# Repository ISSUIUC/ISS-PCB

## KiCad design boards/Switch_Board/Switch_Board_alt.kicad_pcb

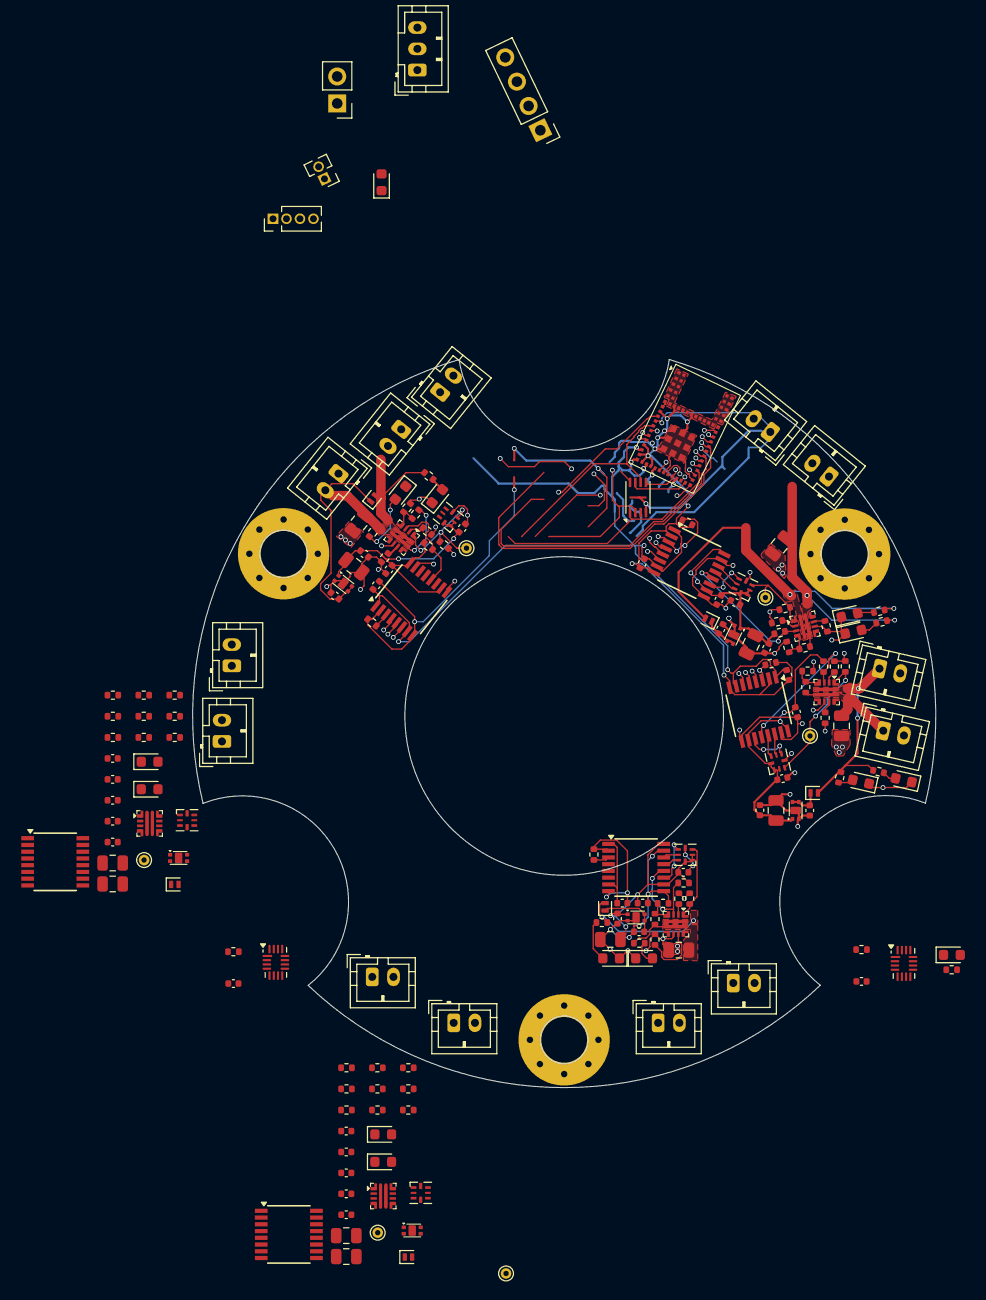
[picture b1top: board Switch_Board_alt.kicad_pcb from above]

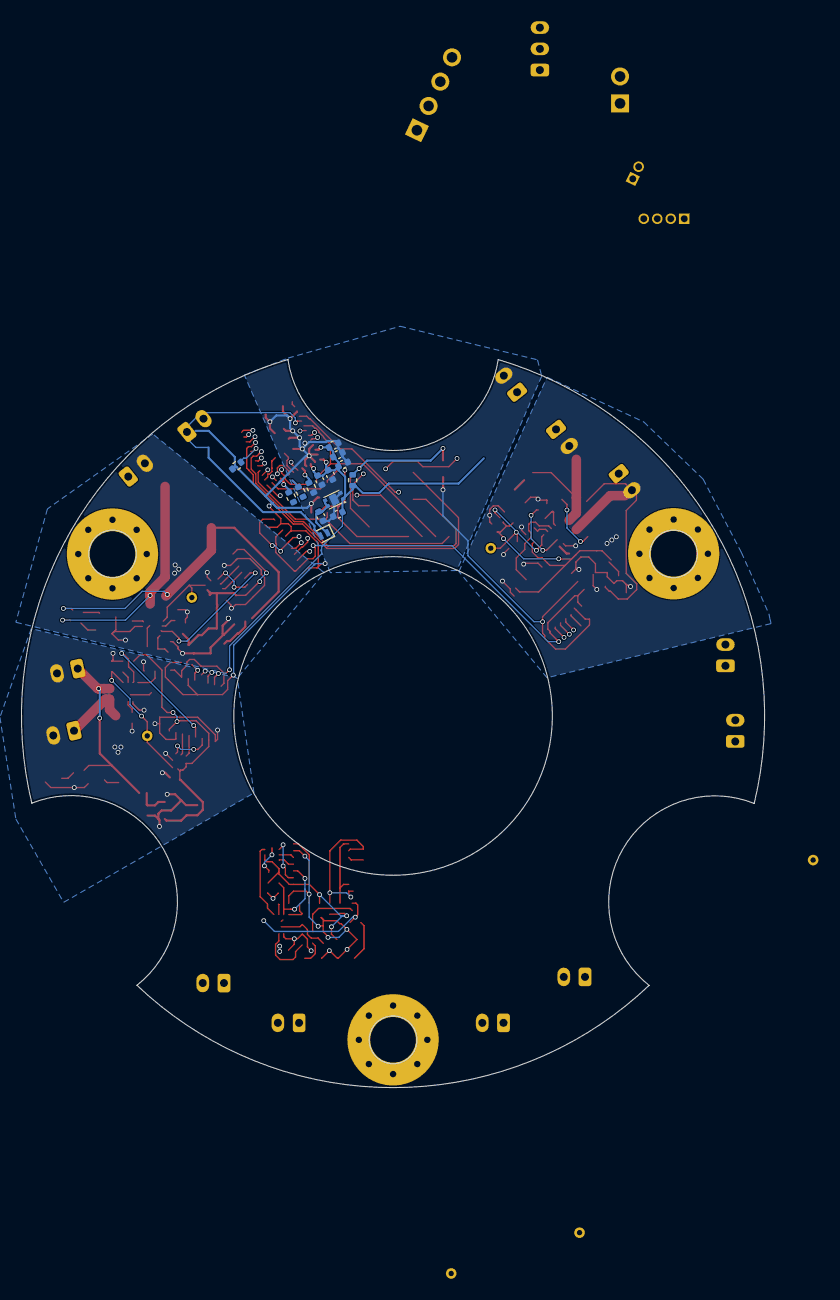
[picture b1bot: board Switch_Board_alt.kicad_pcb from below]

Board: 4 copper layers, 70.0 x 68.6 mm, 187 parts (14 on the bottom side), 126 nets.

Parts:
C101, C103, C104, C105, C108, C109, C201, C202, C203, C301, C302, C303, C401, C402, C403, C501, C502, C503, C601, C602, C603, C701, C702, C703: 100nF; C_0402_1005Metric
C102, C107: 4.7uF; C_0402_1005Metric
C106, C204, C205, C304, C305, C404, C405, C504, C505, C604, C605, C704, C705: 1uF; C_0402_1005Metric
C206, C306, C406, C506, C606, C706: 100uF; C_0805_2012Metric
C207, C307, C407, C507, C607, C707: 22uF; C_0805_2012Metric
D101, D201, D301, D401, D501, D601, D701: SDM05U40CSP-7; D_SOD-882
D102, D202, D203, D302, D303, D402, D403, D502, D503, D602, D603, D702, D703: LED; LED_0603_1608Metric
D103: BLUE_LED; LED_0603_1608Metric
J101, J201, J203, J301, J303, J401, J403, J501, J503, J601, J603, J701, J703: Conn_01x02; JST_PH_B2B-PH-K_1x02_P2.00mm_Vertical
J102: Conn_01x03; JST_PH_B3B-PH-K_1x03_P2.00mm_Vertical
J103: Conn_01x04; PinHeader_1x04_P2.54mm_Vertical
J104: Conn_01x02; PinHeader_1x02_P2.54mm_Vertical
J105: Conn_01x02; PinHeader_1x02_P1.27mm_Vertical
J106: Conn_01x04; PinHeader_1x04_P1.27mm_Vertical
J202, J302, J402, J502, J602, J702: Conn_01x01; TestPoint_THTPad_D1.0mm_Drill0.5mm
R101, R102, R103, R108, R201, R202, R204, R301, R302, R304, R401, R402, R404, R501, R502, R504, R601, R602, R604, R701, R702, R704: 10k; R_0402_1005Metric
R104, R105: 470; R_0402_1005Metric
R106, R107: 4.7k; R_0402_1005Metric
R203, R209, R303, R309, R403, R409, R503, R509, R603, R609, R703, R709: 1k; R_0402_1005Metric
R205, R305, R405, R505, R605, R705: 680; R_0402_1005Metric
R206, R306, R406, R506, R606, R706: 390k; R_0402_1005Metric
R207, R307, R407, R507, R607, R707: 300k; R_0402_1005Metric
R208, R308, R408, R508, R608, R708: 500k; R_0402_1005Metric
U101: W25Q16JLUX; Winbond_USON-8-1EP_3x2mm_P0.5mm_EP0.2x1.6mm
U102: STM32WB1MMC; LGA77_6P5X10_STM
U103, U203, U303, U403, U503, U603, U703: XC6223; Torex_USP-4
U104, U105: TCAL9538; UQFN-16_1.8x2.6mm_P0.4mm
U201, U301, U401, U501, U601, U701: ISO7742; SSOP-16_3.9x4.9mm_P0.635mm
U202, U302, U402, U502, U602, U702: SN74AUP1G74RSER; UQFN-RSE0008A
U204, U304, U404, U504, U604, U704: TPS25947; VQFN-HR-RPW0010A

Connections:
/BOOT: J102.2, R101.2, U102.22 (BOOT0)
/CoinCell_V: D101.2 (A), J101.1, U102.10 (PA8)
/Debug_LED: R105.1, U104.9 (P6)
/EXP_RESET: R102.1, R103.1, U102.13 (PA2), U104.1 (~RESET), U105.1 (~RESET)
/FLASH_CS: J106.1, U101.1 (~CS), U102.33 (PB4)
/FLASH_RESET: U101.7 (~HOLD/~RESET/IO_{3}), U102.29 (PA7)
/GPIO_Clock: R108.2, U102.37 (PA0), U201.4 (INB), U301.4 (INB), U401.4 (INB), U501.4 (INB), U601.4 (INB), U701.4 (INB)
/I2C_SCL: J105.1, R107.1, U102.27 (PB6), U104.12 (SCL), U105.12 (SCL)
/I2C_SDA: J105.2, R106.1, U102.25 (PB7), U104.13 (SDA), U105.13 (SDA)
/Isolated Flip Flops + Switch 1/PG: R204.2, U201.12 (INC), U204.3 (PG/AUXOFF)
/Isolated Flip Flops + Switch 1/Q: J202.1, R202.2, U202.3 (Q), U204.1 (EN/UVLO)
/Isolated Flip Flops + Switch 1/Reg_V: C201.1, C203.1, C205.1, C206.1, R204.1, U201.10 (EN2), U201.16 (VCC2), U202.1 (~PRE), U202.2 (~CLR), U202.8 (VCC), U203.1 (VOUT)
/Isolated Flip Flops + Switch 1/SubBatt_V: D201.2 (A), J201.1, R203.1, U204.5 (IN)
/Isolated Flip Flops + Switch 1/~Q: U201.11 (IND), U202.5 (~Q)
/Isolated Flip Flops + Switch 2/PG: R304.2, U301.12 (INC), U304.3 (PG/AUXOFF)
/Isolated Flip Flops + Switch 2/Q: J302.1, R302.2, U302.3 (Q), U304.1 (EN/UVLO)
/Isolated Flip Flops + Switch 2/Reg_V: C301.1, C303.1, C305.1, C306.1, R304.1, U301.10 (EN2), U301.16 (VCC2), U302.1 (~PRE), U302.2 (~CLR), U302.8 (VCC), U303.1 (VOUT)
/Isolated Flip Flops + Switch 2/SubBatt_V: D301.2 (A), J301.1, R303.1, U304.5 (IN)
/Isolated Flip Flops + Switch 2/~Q: U301.11 (IND), U302.5 (~Q)
/Isolated Flip Flops + Switch 3/PG: R404.2, U401.12 (INC), U404.3 (PG/AUXOFF)
/Isolated Flip Flops + Switch 3/Q: J402.1, R402.2, U402.3 (Q), U404.1 (EN/UVLO)
/Isolated Flip Flops + Switch 3/Reg_V: C401.1, C403.1, C405.1, C406.1, R404.1, U401.10 (EN2), U401.16 (VCC2), U402.1 (~PRE), U402.2 (~CLR), U402.8 (VCC), U403.1 (VOUT)
/Isolated Flip Flops + Switch 3/SubBatt_V: D401.2 (A), J401.1, R403.1, U404.5 (IN)
/Isolated Flip Flops + Switch 3/~Q: U401.11 (IND), U402.5 (~Q)
/Isolated Flip Flops + Switch 4/PG: R504.2, U501.12 (INC), U504.3 (PG/AUXOFF)
/Isolated Flip Flops + Switch 4/Q: J502.1, R502.2, U502.3 (Q), U504.1 (EN/UVLO)
/Isolated Flip Flops + Switch 4/Reg_V: C501.1, C503.1, C505.1, C506.1, R504.1, U501.10 (EN2), U501.16 (VCC2), U502.1 (~PRE), U502.2 (~CLR), U502.8 (VCC), U503.1 (VOUT)
/Isolated Flip Flops + Switch 4/SubBatt_V: D501.2 (A), J501.1, R503.1, U504.5 (IN)
/Isolated Flip Flops + Switch 4/~Q: U501.11 (IND), U502.5 (~Q)
/Isolated Flip Flops + Switch 5/PG: R604.2, U601.12 (INC), U604.3 (PG/AUXOFF)
/Isolated Flip Flops + Switch 5/Q: J602.1, R602.2, U602.3 (Q), U604.1 (EN/UVLO)
/Isolated Flip Flops + Switch 5/Reg_V: C601.1, C603.1, C605.1, C606.1, R604.1, U601.10 (EN2), U601.16 (VCC2), U602.1 (~PRE), U602.2 (~CLR), U602.8 (VCC), U603.1 (VOUT)
/Isolated Flip Flops + Switch 5/SubBatt_V: D601.2 (A), J601.1, R603.1, U604.5 (IN)
/Isolated Flip Flops + Switch 5/~Q: U601.11 (IND), U602.5 (~Q)
/Isolated Flip Flops + Switch 6/PG: R704.2, U701.12 (INC), U704.3 (PG/AUXOFF)
/Isolated Flip Flops + Switch 6/Q: J702.1, R702.2, U702.3 (Q), U704.1 (EN/UVLO)
/Isolated Flip Flops + Switch 6/Reg_V: C701.1, C703.1, C705.1, C706.1, R704.1, U701.10 (EN2), U701.16 (VCC2), U702.1 (~PRE), U702.2 (~CLR), U702.8 (VCC), U703.1 (VOUT)
/Isolated Flip Flops + Switch 6/SubBatt_V: D701.2 (A), J701.1, R703.1, U704.5 (IN)
/Isolated Flip Flops + Switch 6/~Q: U701.11 (IND), U702.5 (~Q)
/NRST: J102.1, U102.23 (NRST)
/PG_ISO_1: U102.28 (PA3), U201.5 (OUTC)
/PG_ISO_2: U104.5 (P3), U301.5 (OUTC)
/PG_ISO_3: U104.4 (P2), U401.5 (OUTC)
/PG_ISO_4: U105.4 (P2), U501.5 (OUTC)
/PG_ISO_5: U105.5 (P3), U601.5 (OUTC)
/PG_ISO_6: U102.9 (PA4), U701.5 (OUTC)
/SPI_MISO: J106.4, U101.2 (DO/IO_{1}), U102.12 (PA6)
/SPI_MOSI: J106.3, U101.5 (DI/IO_{0}), U102.26 (PB5)
/SPI_SCK: J106.2, U101.6 (CLK), U102.11 (PA1)
/SWCLK: J103.2, U102.34 (PA14)
/SWDIO: J103.3, U102.35 (PA13)
/Switch_1: R201.1, U102.30 (PA12), U201.3 (INA)
/Switch_2: R301.1, U104.2 (P0), U301.3 (INA)
/Switch_3: R401.1, U104.3 (P1), U401.3 (INA)
/Switch_4: R501.1, U105.2 (P0), U501.3 (INA)
/Switch_5: R601.1, U105.3 (P1), U601.3 (INA)
/Switch_6: R701.1, U102.32 (PA11), U701.3 (INA)
/UART_RX: J104.1, U102.36 (PA10)
/UART_TX: J104.2, U102.38 (PA9)
/~Q_ISO_1: U102.39 (PA5), U201.6 (OUTD)
/~Q_ISO_2: U104.7 (P4), U301.6 (OUTD)
/~Q_ISO_3: U104.8 (P5), U401.6 (OUTD)
/~Q_ISO_4: U105.8 (P5), U501.6 (OUTD)
/~Q_ISO_5: U105.7 (P4), U601.6 (OUTD)
/~Q_ISO_6: U102.14 (PB8), U701.6 (OUTD)
GND2: C201.2, C203.2, C204.2, C205.2, C206.2, C207.2, C301.2, C303.2, C304.2, C305.2, C306.2, C307.2, C401.2, C403.2, C404.2, C405.2, C406.2, C407.2, C501.2, C503.2, C504.2, C505.2, C506.2, C507.2, C601.2, C603.2, C604.2, C605.2, C606.2, C607.2, C701.2, C703.2, C704.2, C705.2, C706.2, C707.2, D202.1 (K), D203.1 (K), D302.1 (K), D303.1 (K), D402.1 (K), D403.1 (K), D502.1 (K), D503.1 (K), D602.1 (K), D603.1 (K), D702.1 (K), D703.1 (K), J201.2, J203.2, J301.2, J303.2, J401.2, J403.2, J501.2, J503.2, J601.2, J603.2, J701.2, J703.2, R202.1, R205.1, R206.2, R208.2, R302.1, R305.1, R306.2, R308.2, R402.1, R405.1, R406.2, R408.2, R502.1, R505.1, R506.2, R508.2, R602.1, R605.1, R606.2, R608.2, R702.1, R705.1, R706.2, R708.2, U201.9 (GND2), U201.15 (GND2), U202.4 (GND), U203.2 (VSS), U203.5 (EP), U204.8 (GND), U301.9 (GND2), U301.15 (GND2), U302.4 (GND), U303.2 (VSS), U303.5 (EP), U304.8 (GND), U401.9 (GND2), U401.15 (GND2), U402.4 (GND), U403.2 (VSS), U403.5 (EP), U404.8 (GND), U501.9 (GND2), U501.15 (GND2), U502.4 (GND), U503.2 (VSS), U503.5 (EP), U504.8 (GND), U601.9 (GND2), U601.15 (GND2), U602.4 (GND), U603.2 (VSS), U603.5 (EP), U604.8 (GND), U701.9 (GND2), U701.15 (GND2), U702.4 (GND), U703.2 (VSS), U703.5 (EP), U704.8 (GND)
MCU_GND: C101.2, C102.2, C103.2, C104.2, C105.2, C106.2, C107.2, C108.2, C109.2, C202.2, C302.2, C402.2, C502.2, C602.2, C702.2, D102.1 (K), D103.1 (K), J101.2, J102.3, J103.4, R101.1, R108.1, R201.2, R301.2, R401.2, R501.2, R601.2, R701.2, U101.4 (GND), U101.9 (EP), U102.1 (VSS), U102.2 (VSS), U102.3 (VSS), U102.4 (VSS), U102.5 (VSSRF), U102.8 (VSSRF), U102.15 (VSS), U102.17 (VSS), U102.19 (VSS), U102.21 (VSSSMPS), U102.24 (VSS), U102.31 (VSS), U102.43 (VSS), U102.44 (VSS), U102.45 (VSS), U102.46 (VSS), U102.47 (VSS), U102.48 (VSS), U102.49 (VSS), U102.50 (VSS), U102.51 (VSS), U102.52 (VSS), U102.53 (VSS), U102.54 (VSS), U102.55 (VSS), U102.56 (VSS), U102.57 (VSS), U102.58 (VSS), U102.59 (VSS), U102.60 (VSS), U102.61 (VSS), U102.62 (VSS), U102.63 (VSS), U102.64 (VSS), U102.65 (VSS), U102.66 (VSS), U102.67 (VSS), U102.68 (VSS), U102.69 (VSS), U102.70 (VSS), U102.71 (VSS), U102.72 (VSS), U102.73 (VSS), U102.74 (VSS), U102.75 (VSS), U102.76 (VSS), U102.77 (VSS), U103.2 (VSS), U103.5 (EP), U104.6 (GND), U104.16 (A1), U105.6 (GND), U105.15 (A0), U201.2 (GND1), U201.8 (GND1), U301.2 (GND1), U301.8 (GND1), U401.2 (GND1), U401.8 (GND1), U501.2 (GND1), U501.8 (GND1), U601.2 (GND1), U601.8 (GND1), U701.2 (GND1), U701.8 (GND1)
MCU_V: C101.1, C102.1, C103.1, C104.1, C105.1, C107.1, C108.1, C109.1, C202.1, C302.1, C402.1, C502.1, C602.1, C702.1, J103.1, R102.2, R103.2, R104.2, R106.2, R107.2, U101.8 (VCC), U102.16 (VDDA), U102.18 (VBAT), U102.20 (VDDSMPS), U103.1 (VOUT), U104.14 (VCC), U104.15 (A0), U105.14 (VCC), U105.16 (A1), U201.1 (VCC1), U201.7 (EN1), U301.1 (VCC1), U301.7 (EN1), U401.1 (VCC1), U401.7 (EN1), U501.1 (VCC1), U501.7 (EN1), U601.1 (VCC1), U601.7 (EN1), U701.1 (VCC1), U701.7 (EN1)
unnamed: C106.1, D101.1 (K), U103.3 (CE), U103.4 (VIN)
unnamed: D102.2 (A), R104.1
unnamed: D103.2 (A), R105.2
unnamed: C204.1, D201.1 (K), U203.3 (CE), U203.4 (VIN)
unnamed: D202.2 (A), R203.2
unnamed: D203.2 (A), R209.2
unnamed: C304.1, D301.1 (K), U303.3 (CE), U303.4 (VIN)
unnamed: D302.2 (A), R303.2
unnamed: D303.2 (A), R309.2
unnamed: C404.1, D401.1 (K), U403.3 (CE), U403.4 (VIN)
unnamed: D402.2 (A), R403.2
unnamed: D403.2 (A), R409.2
unnamed: C504.1, D501.1 (K), U503.3 (CE), U503.4 (VIN)
unnamed: D502.2 (A), R503.2
unnamed: D503.2 (A), R509.2
unnamed: C604.1, D601.1 (K), U603.3 (CE), U603.4 (VIN)
unnamed: D602.2 (A), R603.2
unnamed: D603.2 (A), R609.2
unnamed: C704.1, D701.1 (K), U703.3 (CE), U703.4 (VIN)
unnamed: D702.2 (A), R703.2
unnamed: D703.2 (A), R709.2
unnamed: C207.1, J203.1, R207.1, R209.1, U204.6 (OUT)
unnamed: C307.1, J303.1, R307.1, R309.1, U304.6 (OUT)
unnamed: C407.1, J403.1, R407.1, R409.1, U404.6 (OUT)
unnamed: C507.1, J503.1, R507.1, R509.1, U504.6 (OUT)
unnamed: C607.1, J603.1, R607.1, R609.1, U604.6 (OUT)
unnamed: C707.1, J703.1, R707.1, R709.1, U704.6 (OUT)
unnamed: U102.6 (ANT_IN), U102.7 (ANT_OUT)
unnamed: U201.14 (OUTA), U202.6 (D)
unnamed: U201.13 (OUTB), U202.7 (CLK)
unnamed: R205.2, U204.9 (ILM)
unnamed: R206.1, U204.2 (OVLO/OVCSEL)
unnamed: R207.2, R208.1, U204.4 (PGTH/NFLT)
unnamed: U301.14 (OUTA), U302.6 (D)
unnamed: U301.13 (OUTB), U302.7 (CLK)
unnamed: R305.2, U304.9 (ILM)
unnamed: R306.1, U304.2 (OVLO/OVCSEL)
unnamed: R307.2, R308.1, U304.4 (PGTH/NFLT)
unnamed: U401.14 (OUTA), U402.6 (D)
unnamed: U401.13 (OUTB), U402.7 (CLK)
unnamed: R405.2, U404.9 (ILM)
unnamed: R406.1, U404.2 (OVLO/OVCSEL)
unnamed: R407.2, R408.1, U404.4 (PGTH/NFLT)
unnamed: U501.14 (OUTA), U502.6 (D)
unnamed: U501.13 (OUTB), U502.7 (CLK)
unnamed: R505.2, U504.9 (ILM)
unnamed: R506.1, U504.2 (OVLO/OVCSEL)
unnamed: R507.2, R508.1, U504.4 (PGTH/NFLT)
unnamed: U601.14 (OUTA), U602.6 (D)
unnamed: U601.13 (OUTB), U602.7 (CLK)
unnamed: R605.2, U604.9 (ILM)
unnamed: R606.1, U604.2 (OVLO/OVCSEL)
unnamed: R607.2, R608.1, U604.4 (PGTH/NFLT)
unnamed: U701.14 (OUTA), U702.6 (D)
unnamed: U701.13 (OUTB), U702.7 (CLK)
unnamed: R705.2, U704.9 (ILM)
unnamed: R706.1, U704.2 (OVLO/OVCSEL)
unnamed: R707.2, R708.1, U704.4 (PGTH/NFLT)

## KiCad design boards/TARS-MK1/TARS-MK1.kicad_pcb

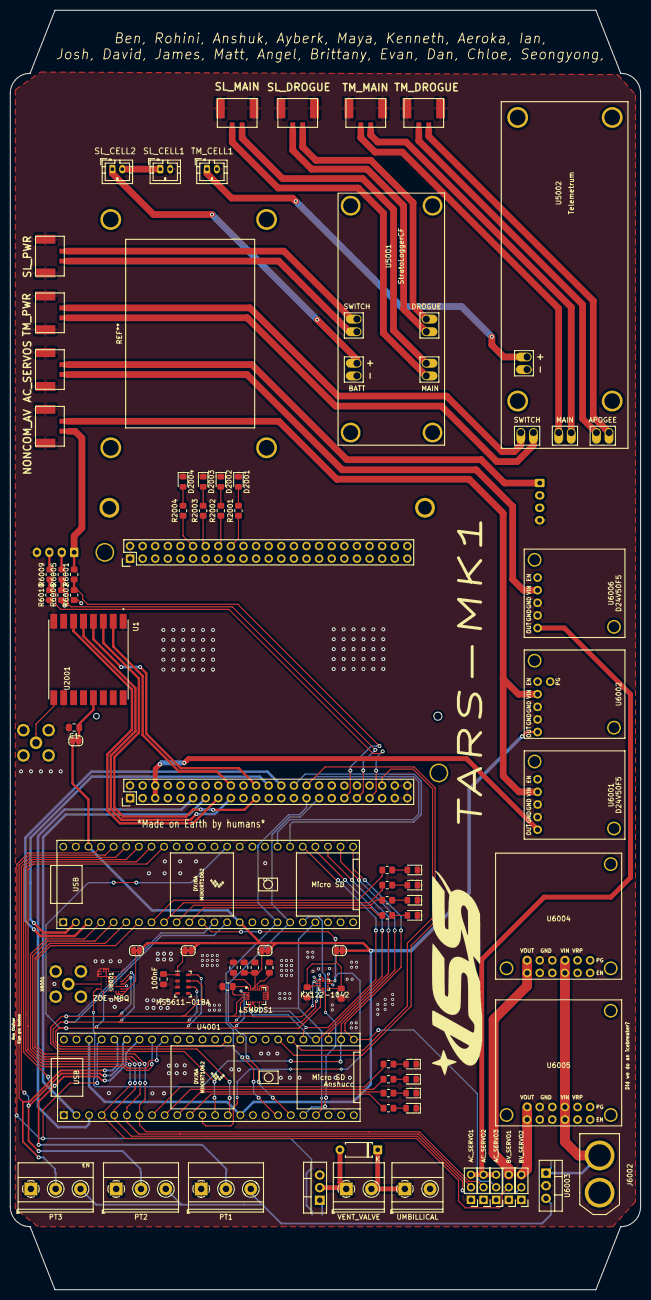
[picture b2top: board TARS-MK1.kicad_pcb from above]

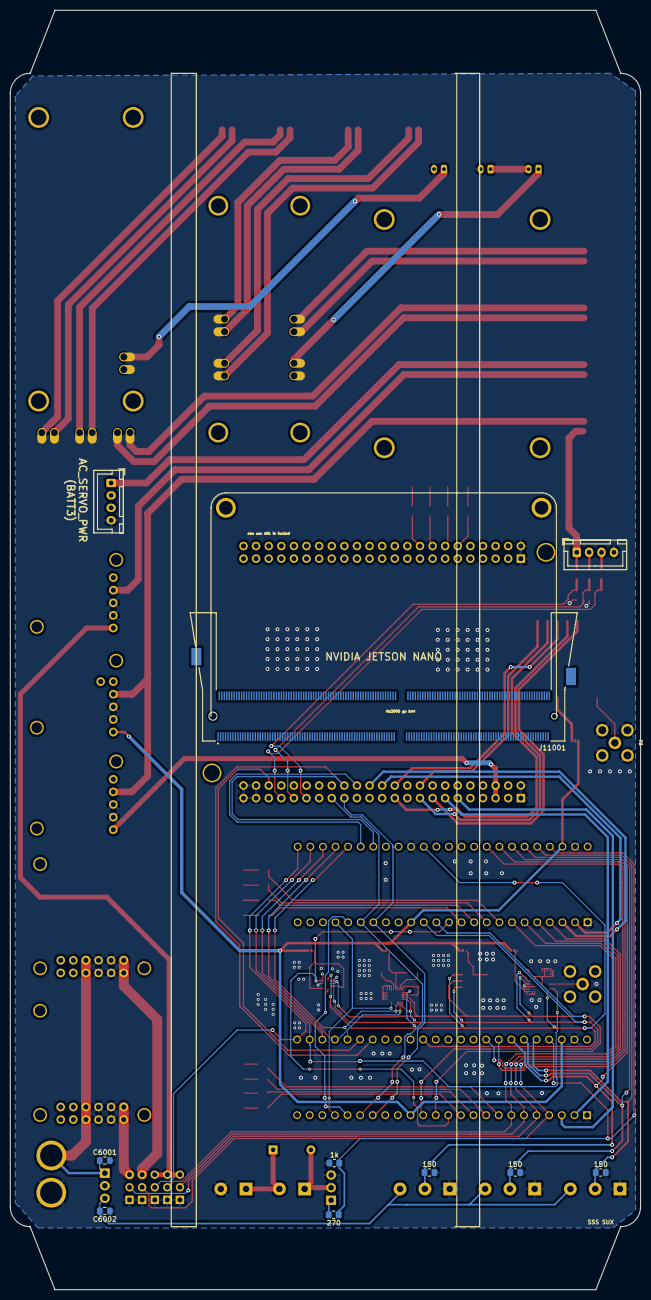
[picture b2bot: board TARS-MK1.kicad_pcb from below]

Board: 2 copper layers, 127.0 x 257.8 mm, 96 parts (11 on the bottom side), 106 nets.

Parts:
C1, C7006, C7007, C7008: 100nF; C_0805_2012Metric_Pad1.18x1.45mm_HandSolder
C6001, C6002: 100nF; C_0805_2012Metric_Pad1.15x1.40mm_HandSolder
C7001: 10 nF; C_0805_2012Metric_Pad1.18x1.45mm_HandSolder
C7002, C7003, C7004: 100 nF; C_0805_2012Metric_Pad1.18x1.45mm_HandSolder
C7005: 10 uF; C_0805_2012Metric_Pad1.18x1.45mm_HandSolder
D2001, D2002, D2003, D2004, D4001, D4002, D4003, D4004, D9001, D9002, D9003, D9004: LED; LED_0805_2012Metric_Pad1.15x1.40mm_HandSolder
D3001: D; D_A-405_P7.62mm_Horizontal
J3001: VENT_VALVE; TerminalBlock_Phoenix_MKDS-1,5-2-5.08_1x02_P5.08mm_Horizont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
J3002: BV_SERVO1; PinHeader_1x03_P2.54mm_Vertical
J3003: BV_SERVO2; PinHeader_1x03_P2.54mm_Vertical
J3004: PT1; TerminalBlock_Phoenix_MKDS-1,5-3_1x03_P5.00mm_Horizontal
J3005: PT2; TerminalBlock_Phoenix_MKDS-1,5-3_1x03_P5.00mm_Horizontal
J3006: PT3; TerminalBlock_Phoenix_MKDS-1,5-3_1x03_P5.00mm_Horizontal
J3007: UMBILLICAL; TerminalBlock_Phoenix_MKDS-1,5-2-5.08_1x02_P5.08mm_Horizont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
J5001, J5002, J5003, J5004, J5005, J5006, J6006, J6009: 505575-0271
J6001: BATT1; JST_XH_B4B-XH-A_1x04_P2.50mm_Vertical
J6002: BATT2_XT60; XT60
J6004: BATT4_CELL2; JST_PH_B2B-PH-K_1x02_P2.00mm_Vertical
J6005: BATT4_CELL1; JST_PH_B2B-PH-K_1x02_P2.00mm_Vertical
J6007: BATT5_CELL1; JST_PH_B2B-PH-K_1x02_P2.00mm_Vertical
J6008: BATT3_JST; JST_XH_B4B-XH-A_1x04_P2.50mm_Vertical
J7001: AC_SERVO1; PinHeader_1x03_P2.54mm_Vertical
J7002: AC_SERVO2; PinHeader_1x03_P2.54mm_Vertical
J7003: AC_SERVO3; PinHeader_1x03_P2.54mm_Vertical
J11001: 2309413-1; JETSON_NANO
JP2, JP3, JP4, JP5, JP6: Jumper_NC_Small; SolderJumper-2_P1.3mm_Bridged_RoundedPad1.0x1.5mm
Q3001: IRF540N; TO-220-3_Vertical
R2001, R2002, R2003, R2004, R4001, R4002, R4003, R4004, R9001, R9002, R9003, R9004: 470; R_0805_2012Metric_Pad1.20x1.40mm_HandSolder
R3001: 270; R_0805_2012Metric_Pad1.20x1.40mm_HandSolder
R3002: 1k; R_0805_2012Metric_Pad1.20x1.40mm_HandSolder
R3003, R3004, R3005: 150; R_0805_2012Metric_Pad1.20x1.40mm_HandSolder
R6001, R6005, R6009: 150k; R_0805_2012Metric_Pad1.20x1.40mm_HandSolder
R6002: 23k; R_0805_2012Metric_Pad1.20x1.40mm_HandSolder
R6006: 37.5k; R_0805_2012Metric_Pad1.20x1.40mm_HandSolder
R6010: 100k; R_0805_2012Metric_Pad1.20x1.40mm_HandSolder
U1: RFM95W-915S2; XCVR_RFM95W_915S2
U2001: Socket_BeagleBone_Black
U4001, U9001: Teensy4.1_bare; Teensy41_bare
U5001: StratoLoggerCF; StratologgerCF
U5002: Telemetrum
U6001, U6006: D24V50F5
U6002: D36V28F3
U6003: LM7809_TO220; TO-220-3_Vertical
U6004, U6005: D36V50F6; D36V50F6-TARS
U7001: LSM9DS1; LGA-24L_3x3.5mm_P0.43mm
U7002: KX122-1042; LGA-12_2x2mm_P0.5mm
U7003: MS5611-01BA; LGA-8_3x5mm_P1.25mm
U8001: ZOE-M8Q; ZOE-M8
X1, X8001: SMACONNECTOR; SMA90_DIP

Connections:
3V3_MCU_SUPPLY: JP2.1, JP3.1, JP4.1, JP5.1, JP6.2, U4001.15, U4001.46, U6002.5, U9001.15, U9001.46
5V_AC_SERVO0: J7001.3, J7002.3, J7003.3, U6006.5
5V_MPU_SUPPLY: U2001.5, U2001.6, U6001.5
6V_HYBRID_SERVO0: J3002.3, U6004.6, U6004.12
6V_HYBRID_SERVO1: J3003.3, U6005.6, U6005.12
9V_PT_SUPPLY: C6002.2, J3004.3, J3005.3, J3006.3, U6003.3
AC_MCU_RX1: U2001.24, U9001.2
AC_MCU_SPI1_CS1: U2001.28, U9001.30
AC_MCU_TX1: U2001.26, U9001.3
AC_SERVO0: J7001.2, U4001.6, U9001.6
AC_SERVO1: J7002.2, U4001.7, U9001.7
AC_SERVO2: J7003.2, U4001.25, U9001.25
BATT1_CELL1: R6009.1, R6010.2, U2001.39
BATT1_CELL2: R6005.1, R6006.2, U2001.37
BATT1_CELL3: R6001.1, R6002.2, U2001.35
GND: C1.2, C6001.2, C6002.1, C7001.1, C7002.2, C7003.2, C7004.2, C7005.2, C7006.2, C7007.2, C7008.1, D2001.1, D2002.1, D2003.1, D2004.1, D4001.1, D4002.1, D4003.1, D4004.1, D9001.1, D9002.1, D9003.1, D9004.1, J3002.1, J3003.1, J3004.1, J3005.1, J3006.1, J3007.2, J5001.3, J5001.4, J5002.3, J5002.4, J5003.3, J5003.4, J5004.3, J5004.4, J5005.3, J5005.4, J5006.3, J5006.4, J6001.4, J6002.1, J6005.2, J6006.3, J6006.4, J6007.2, J6008.4, J6009.3, J6009.4, J7001.1, J7002.1, J7003.1, Q3001.3, R3002.2, R3003.1, R3004.1, R3005.1, R6002.1, R6006.1, R6010.1, U1.1, U1.8, U1.10, U2001.1, U2001.2, U2001.43, U2001.44, U2001.45, U2001.46, U2001.47, U2001.48, U4001.1, U4001.34, U4001.47, U5001.GND, U5002.GND, U6001.3, U6001.4, U6002.3, U6002.4, U6003.2, U6004.4, U6004.5, U6004.10, U6004.11, U6005.4, U6005.5, U6005.10, U6005.11, U6006.3, U6006.4, U7001.14, U7001.15, U7001.16, U7001.17, U7001.18, U7001.19, U7001.20, U7002.9, U7003.2, U7003.3, U8001.P$A1, U8001.P$A3, U8001.P$A5, U8001.P$A7, U8001.P$A8, U8001.P$A9, U8001.P$B9, U8001.P$C7, U8001.P$C9, U8001.P$D4, U8001.P$D6, U8001.P$D9, U8001.P$E7, U8001.P$F7, U8001.P$G3, U8001.P$G6, U8001.P$G7, U8001.P$J3, U8001.P$J9, U9001.1, U9001.34, U9001.47, X1.GND1, X1.GND2, X1.GND3, X1.GND4, X8001.GND1, X8001.GND2, X8001.GND3, X8001.GND4
HYBRID_PT1: J3004.2, R3003.2, U4001.42, U9001.42
HYBRID_PT2: J3005.2, R3004.2, U4001.43, U9001.43
HYBRID_PT3: J3006.2, R3005.2, U4001.44, U9001.44
HYBRID_SERVO1: J3002.2, U4001.4, U9001.4
HYBRID_SERVO2: J3003.2, U4001.5, U9001.5
HYBRID_VENT_TRIGGER: R3001.1, R3002.1, U4001.45, U9001.45
HYB_MCU_RX1: U2001.13, U4001.2
HYB_MCU_SPI1_CS1: U2001.42, U4001.30
HYB_MCU_TX1: U2001.11, U4001.3
IMU0_INT1: U4001.20, U7002.5, U9001.20
IMU1_INT1: U4001.21, U7001.11, U9001.21
MCU_I2C0_SCL: U4001.41, U9001.41
MCU_I2C0_SDA: U4001.40, U9001.40
MCU_SPI0_CS10: U4001.12, U7002.10, U9001.12
MCU_SPI0_CS34: U4001.26, U8001.P$A2, U9001.26
MCU_SPI0_CS35: U7003.4, U7003.5
MCU_SPI0_CS36: U4001.28, U7001.7, U9001.28
MCU_SPI0_CS37: U4001.29, U7001.8, U9001.29
MCU_SPI0_MISO: U4001.14, U7001.5, U7001.6, U7002.1, U7003.6, U8001.P$J5, U9001.14
MCU_SPI0_MOSI: U4001.13, U7001.4, U7002.2, U7003.7, U8001.P$J4, U9001.13
MCU_SPI0_SCK: U4001.35, U7001.2, U7002.12, U7003.8, U8001.P$B1, U9001.35
MCU_SPI1_CS35: U4001.27, U9001.27
MCU_SPI1_MISO: U2001.30, U4001.31, U9001.31
MCU_SPI1_MOSI: U2001.29, U4001.18, U9001.18
MCU_SPI1_SCK: U2001.31, U4001.19, U9001.19
MPU_SPI0_CS0: U1.5, U2001.17
MPU_SPI0_MISO: U1.2, U2001.18
MPU_SPI0_MOSI: U1.3, U2001.21
MPU_SPI0_SCLK: U1.4, U2001.22
unnamed: C1.1, JP6.1, U1.13
unnamed: C6001.1, J6002.2, U6003.1, U6004.3, U6004.9, U6005.3, U6005.9
unnamed: C7001.2, U7001.21
unnamed: C7002.1, U7001.24
unnamed: C7003.1, C7004.1, C7005.1, JP2.2, U7001.1, U7001.3, U7001.22, U7001.23
unnamed: C7006.1, C7007.1, JP3.2, U7002.3, U7002.7
unnamed: C7008.2, JP4.2, U7003.1
unnamed: D2001.2, R2001.2
unnamed: D2002.2, R2002.2
unnamed: D2003.2, R2003.2
unnamed: D2004.2, R2004.2
unnamed: D3001.1, J3001.2, J3007.1
unnamed: D3001.2, J3001.1, Q3001.2
unnamed: D4001.2, R4001.2
unnamed: D4002.2, R4002.2
unnamed: D4003.2, R4003.2
unnamed: D4004.2, R4004.2
unnamed: D9001.2, R9001.2
unnamed: D9002.2, R9002.2
unnamed: D9003.2, R9003.2
unnamed: D9004.2, R9004.2
unnamed: J5001.1, U5001.SWITCH2
unnamed: J5001.2, U5001.SWITCH1
unnamed: J5002.1, U5002.SWITCH1
unnamed: J5002.2, U5002.SWITCH2
unnamed: J5003.1, U5001.DROGUE2
unnamed: J5003.2, U5001.DROGUE1
unnamed: J5004.1, U5001.MAIN2
unnamed: J5004.2, U5001.MAIN1
unnamed: J5005.1, U5002.APOGEE2
unnamed: J5005.2, U5002.APOGEE1
unnamed: J5006.1, U5002.MAIN2
unnamed: J5006.2, U5002.MAIN1
unnamed: J6001.1, J6006.1, R6001.2
unnamed: J6001.2, R6005.2
unnamed: J6001.3, R6009.2
unnamed: J6004.2, J6005.1
unnamed: J6006.2, U6001.2, U6002.2
unnamed: J6008.1, J6009.2
unnamed: J6009.1, U6006.2
unnamed: J11001.S1, J11001.S2
unnamed: JP5.2, U8001.P$G1, U8001.P$H1, U8001.P$J1, U8001.P$J2
unnamed: Q3001.1, R3001.2
unnamed: R2001.1, U2001.64
unnamed: R2002.1, U2001.62
unnamed: R2003.1, U2001.60
unnamed: R2004.1, U2001.58
unnamed: R4001.1, U4001.8
unnamed: R4002.1, U4001.9
unnamed: R4003.1, U4001.10
unnamed: R4004.1, U4001.11
unnamed: R9001.1, U9001.8
unnamed: R9002.1, U9001.9
unnamed: R9003.1, U9001.10
unnamed: R9004.1, U9001.11
unnamed: U1.9, X1.ANTENNA
unnamed: U8001.P$A4, X8001.ANTENNA
unnamed: U8001.P$G9, U8001.P$H9
SL_PWR: J6004.1, U5001.BATT
TLM_RESET: U1.6, U2001.15
TM_PWR: J6007.1, U5002.BATT

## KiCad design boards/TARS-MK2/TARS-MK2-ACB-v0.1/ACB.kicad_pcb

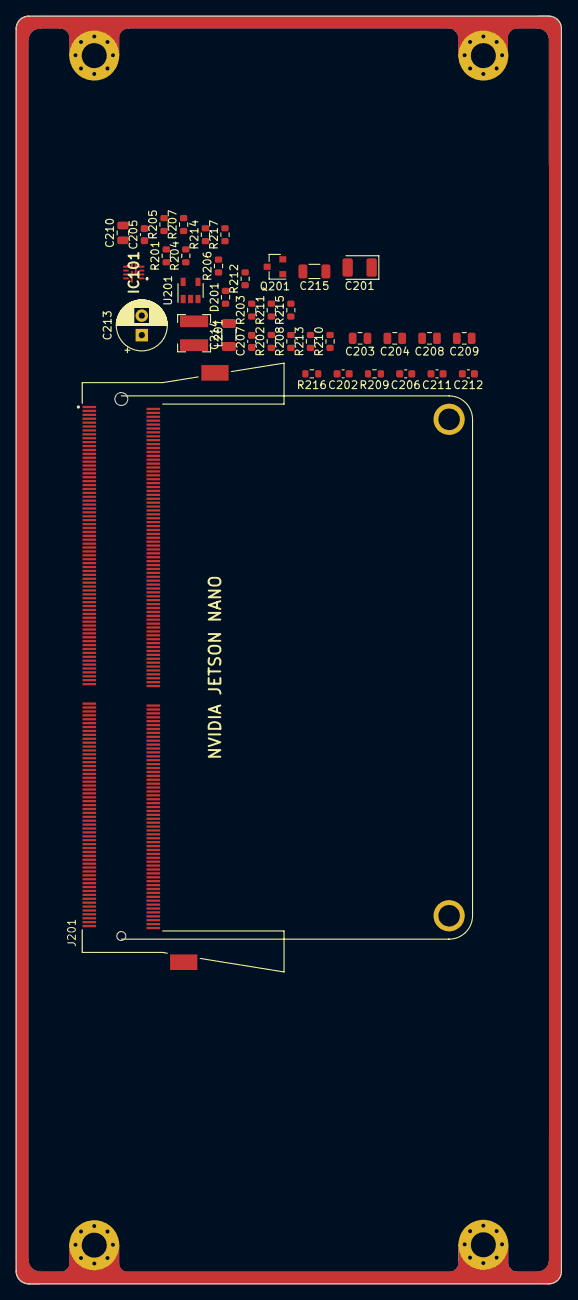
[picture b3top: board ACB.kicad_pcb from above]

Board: 2 copper layers, 69.9 x 162.4 mm, 38 parts (0 on the bottom side), 29 nets, no tracks yet.

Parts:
C201: 100uF; CP_EIA-3528-12_Kemet-T
C202: 0.1uF; C_0603_1608Metric
C203, C204, C208, C209, C210: 22uF; C_0805_2012Metric
C205, C206, C211, C212: 1uF; C_0603_1608Metric
C207: 33pF; C_0603_1608Metric
C213: 560uF; CP_Radial_D6.3mm_P2.50mm
C214, C215: 100uF; C_1206_3216Metric
D201: Green; R_0603_1608Metric
IC101: MP2384GG-P; MP2384GGP
J201: 2309413-1; Jetson_Nano
L201: 2.2uH; L_Bourns-SRN4018
Q201: DMN2230U; SOT-23
R201, R209: 10K; R_0603_1608Metric
R202, R203, R204, R205, R206, R212: 0; R_0603_1608Metric
R207: 40.2K; R_0603_1608Metric
R208: 8.87K; R_0603_1608Metric
R210, R211, R213, R215, R216, R217: 47K; R_0603_1608Metric
R214: 1.8K; R_0603_1608Metric
U201: TLV70018_SOT23-5; SOT-23-5

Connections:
/3V3_IO_PG: IC101.5, IC101.11, R201.2, U201.3
/CAM_I2C_SCL: J201.213, R216.2
/CAM_I2C_SDA: J201.215, R217.2
/I2C0_SCL: J201.185, R210.2
/I2C0_SDA: J201.187, R211.2
/I2C1_SCL: J201.189, R213.2
/I2C1_SDA: J201.191, R215.2
/PWR_BTN: J201.240, R209.2
/PWR_LED_CTRL: J201.127, R212.1
/SPI0_CS0: J201.95, J201.110
/SPI0_CS1: J201.97, J201.112
/SPI0_MISO: J201.93, J201.108
/SPI0_MOSI: J201.89, J201.104
/SPI0_SCK: J201.91, J201.106
/VDD_1V8: C212.1, U201.5
/VDD_3V3_SYS: C208.1, C209.1, C210.1, C211.1, L201.2, R201.1, R206.1, R210.1, R211.1, R213.1, R215.1, R216.1, R217.1, U201.1
/VDD_5V_IN: C201.1, C202.1, C203.1, C204.1, C213.1, C214.1, C215.1, D201.2, IC101.1, J201.251, J201.252, J201.253, J201.254, J201.255, J201.256, J201.257, J201.258, J201.259, J201.260, R209.1
GND: C201.2, C202.2, C203.2, C204.2, C205.2, C208.2, C209.2, C210.2, C211.2, C212.2, C213.2, C214.2, C215.2, IC101.2, IC101.3, IC101.4, IC101.9, J201.1, J201.2, J201.7, J201.8, J201.13, J201.14, J201.19, J201.20, J201.25, J201.26, J201.31, J201.32, J201.37, J201.38, J201.43, J201.44, J201.49, J201.50, J201.55, J201.56, J201.61, J201.62, J201.67, J201.68, J201.73, J201.74, J201.79, J201.80, J201.85, J201.86, J201.102, J201.107, J201.113, J201.119, J201.125, J201.129, J201.132, J201.135, J201.138, J201.141, J201.144, J201.146, J201.147, J201.152, J201.153, J201.158, J201.159, J201.164, J201.165, J201.170, J201.171, J201.176, J201.177, J201.200, J201.201, J201.217, J201.231, J201.241, J201.242, J201.243, J201.244, J201.245, J201.246, J201.247, J201.248, J201.249, J201.250, J201.S1, J201.S2, Q201.2, R208.2, U201.2
unnamed: C205.1, IC101.8
unnamed: C206.1, R202.2
unnamed: C206.2, IC101.6, L201.1, R203.1
unnamed: C207.1, R203.2, R205.1
unnamed: C207.2, R206.2, R207.1
unnamed: D201.1, R214.1
unnamed: IC101.7, R202.1
unnamed: IC101.10, R204.1
unnamed: Q201.1, R212.2
unnamed: Q201.3, R214.2
unnamed: R204.2, R205.2, R207.2, R208.1

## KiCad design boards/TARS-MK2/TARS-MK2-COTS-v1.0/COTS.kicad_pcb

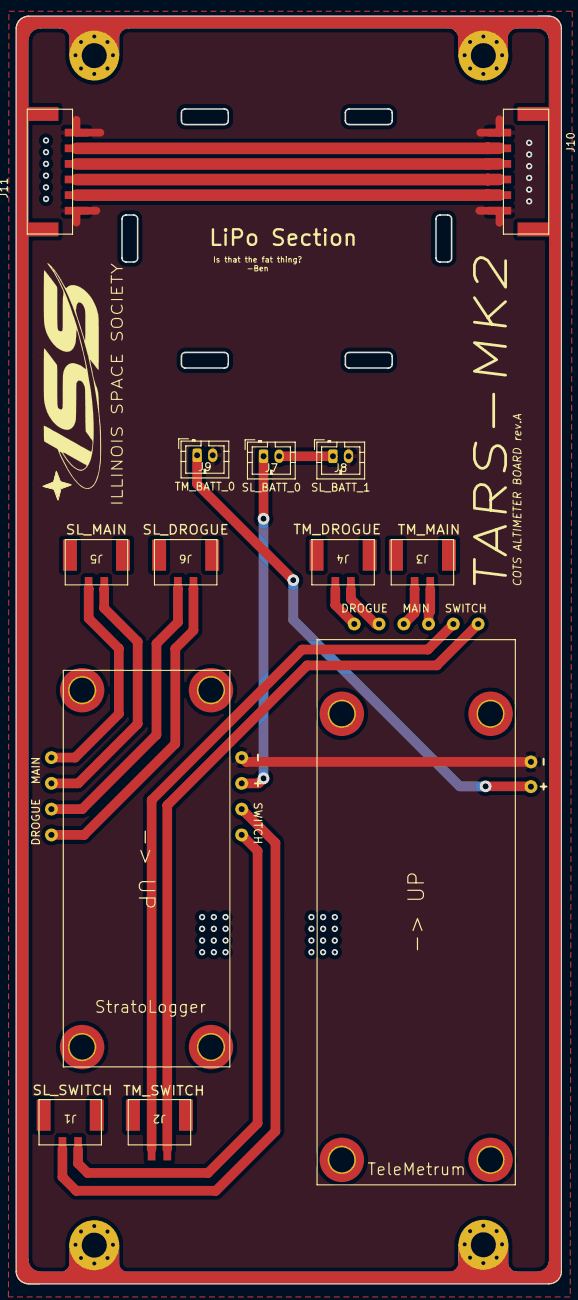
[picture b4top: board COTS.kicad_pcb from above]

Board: 2 copper layers, 69.9 x 162.4 mm, 13 parts (0 on the bottom side), 20 nets.

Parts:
A1: StratoLogger
A2: TeleMetrum
J1: SL_SWITCH; 505575-0271
J2: TM_SWITCH; 505575-0271
J3: TM_MAIN; 505575-0271
J4: TM_DROGUE; 505575-0271
J5: SL_MAIN; 505575-0271
J6: SL_DROGUE; 505575-0271
J7: SL_BATT_0; JST_PH_B2B-PH-K_1x02_P2.00mm_Vertical
J8: SL_BATT_1; JST_PH_B2B-PH-K_1x02_P2.00mm_Vertical
J9: TM_BATT_0; JST_PH_B2B-PH-K_1x02_P2.00mm_Vertical
J10, J11: 505578-0671

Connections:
unnamed: A1.1, J1.2
unnamed: A1.2, J1.1
unnamed: A1.5, J6.2
unnamed: A1.6, J6.1
unnamed: A1.7, J5.2
unnamed: A1.8, J5.1
unnamed: A2.3, J2.2
unnamed: A2.4, J2.1
unnamed: A2.5, J3.2
unnamed: A2.6, J3.1
unnamed: A2.7, J4.2
unnamed: A2.8, J4.1
unnamed: J7.2, J8.1
unnamed: J10.2, J11.5
unnamed: J10.3, J11.4
unnamed: J10.4, J11.3
unnamed: J10.5, J11.2
SL_POWER_NEGATIVE: A1.4, A2.2, J8.2, J9.2, J10.1, J10.6, J11.1, J11.6
SL_POWER_POSITIVE: A1.3, J7.1
TM_POWER_POSITIVE: A2.1, J9.1

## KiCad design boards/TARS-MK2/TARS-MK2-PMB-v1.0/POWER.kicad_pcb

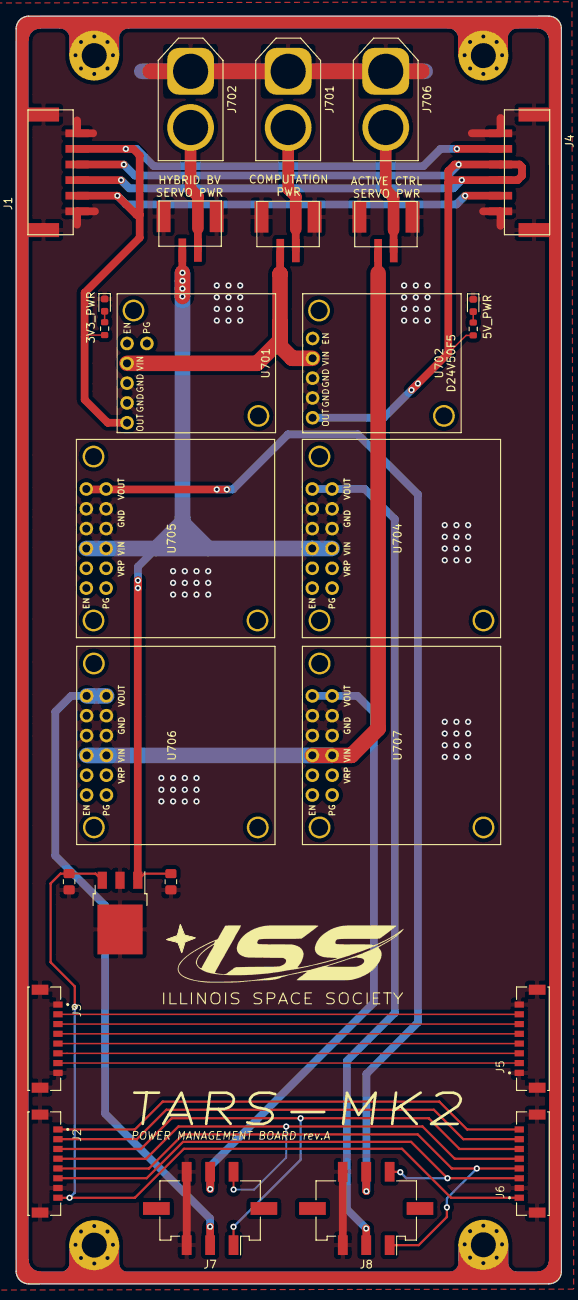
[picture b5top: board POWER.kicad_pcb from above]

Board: 2 copper layers, 69.9 x 162.4 mm, 27 parts (0 on the bottom side), 28 nets.

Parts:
C701, C702: 100nF; C_0805_2012Metric_Pad1.18x1.45mm_HandSolder
D101, D102: LED; LED_0603_1608Metric
J1, J4: 505578-0671
J2, J3, J5, J6: 505567-0871; MOLEX_505567-0871
J7, J8: Conn_02x03_Top_Bottom_MountingPin; Molex_Micro-Fit_3.0_43045-0618_2x03-1MP_P3.00mm_Vertical
J101, J102, J103: 505575-0271
J701, J702, J706: XT60; AMASS_XT60-M_1x02_P7.20mm_Vertical
R101, R102: 1k; R_0603_1608Metric
U701: D36V28F3
U702: D24V50F5
U703: LM7809_TO220; TO-252-3_TabPin2
U704, U705, U706, U707: D36V50F6; D36V50F6-TARS

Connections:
3V3: J1.2, J1.5, J4.2, J4.5, R101.1, U701.5
5V: J1.3, J1.4, J4.3, J4.4, R102.1, U702.5
6V_AC_SERVO1: J7.2, U706.6, U706.12
6V_AC_SERVO2: J7.5, U707.6, U707.12
6V_HYBRID_SERVO3: J8.2, U704.6, U704.12
6V_HYBRID_SERVO4: J8.5, U705.6, U705.12
9V_PT_SUPPLY: C701.1, J2.8, J6.1, U703.3
B2B_SERVO1: J2.3, J6.6, J7.1
B2B_SERVO2: J2.4, J6.5, J7.4
B2B_SERVO3: J2.5, J6.4, J8.1
B2B_SERVO4: J2.6, J6.3, J8.4
GND: C701.2, C702.2, D101.1, D102.1, J1.1, J1.6, J1.P1, J1.P2, J2.7, J2.P1, J2.P2, J3.1, J3.8, J3.P1, J3.P2, J4.1, J4.6, J4.P1, J4.P2, J5.1, J5.8, J5.P1, J5.P2, J6.2, J6.P1, J6.P2, J7.3, J7.6, J8.3, J8.6, J101.3, J101.4, J102.3, J102.4, J103.3, J103.4, J701.1, J702.1, J706.1, U701.3, U701.4, U702.3, U702.4, U703.2, U704.4, U704.5, U704.10, U704.11, U705.4, U705.5, U705.10, U705.11, U706.4, U706.5, U706.10, U706.11, U707.4, U707.5, U707.10, U707.11
unnamed: C702.1, J102.1, U703.1, U704.3, U704.9, U705.3, U705.9
unnamed: D101.2, R101.2
unnamed: D102.2, R102.2
unnamed: J2.1, J6.8
unnamed: J2.2, J6.7
unnamed: J3.2, J5.7
unnamed: J3.3, J5.6
unnamed: J3.4, J5.5
unnamed: J3.5, J5.4
unnamed: J3.6, J5.3
unnamed: J3.7, J5.2
unnamed: J101.1, U701.2, U702.2
unnamed: J101.2, J701.2
unnamed: J102.2, J702.2
unnamed: J103.1, U706.3, U706.9, U707.3, U707.9
unnamed: J103.2, J706.2
